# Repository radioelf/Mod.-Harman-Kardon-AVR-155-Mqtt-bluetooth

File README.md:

# Mod.-Harman-Kardon-AVR-155-Mqtt-bluetooth
Modificación amplificador Harman Kardon AVR 155, con un ESP32 para poder controlar desde MQTT y usar el modulo UDA1334a para poder reproducir música a través de bluetooth

  Creative Commons License Disclaimer
  UNLESS OTHERWISE MUTUALLY AGREED TO BY THE PARTIES IN WRITING, LICENSOR OFFERS THE WORK AS-IS
  AND MAKES NO REPRESENTATIONS OR WARRANTIES OF ANY KIND CONCERNING THE WORK, EXPRESS, IMPLIED,
  STATUTORY OR OTHERWISE, INCLUDING, WITHOUT LIMITATION, WARRANTIES OF TITLE, MERCHANTIBILITY,
  FITNESS FOR A PARTICULAR PURPOSE, NONINFRINGEMENT, OR THE ABSENCE OF LATENT OR OTHER DEFECTS,
  ACCURACY, OR THE PRESENCE OF ABSENCE OF ERRORS, WHETHER OR NOT DISCOVERABLE. SOME JURISDICTIONS
  DO NOT ALLOW THE EXCLUSION OF IMPLIED WARRANTIES, SO SUCH EXCLUSION MAY NOT APPLY TO YOU.
  EXCEPT TO THE EXTENT REQUIRED BY APPLICABLE LAW, IN NO EVENT WILL LICENSOR BE LIABLE TO YOU
  ON ANY LEGAL THEORY FOR ANY SPECIAL, INCIDENTAL, CONSEQUENTIAL, PUNITIVE OR EXEMPLARY DAMAGES
  ARISING OUT OF THIS LICENSE OR THE USE OF THE WORK, EVEN IF LICENSOR HAS BEEN ADVISED OF THE
  POSSIBILITY OF SUCH DAMAGES.
  http://creativecommons.org/licenses/by-sa/3.0/
  Author: Radioelf  http://radioelf.blogspot.com.es/

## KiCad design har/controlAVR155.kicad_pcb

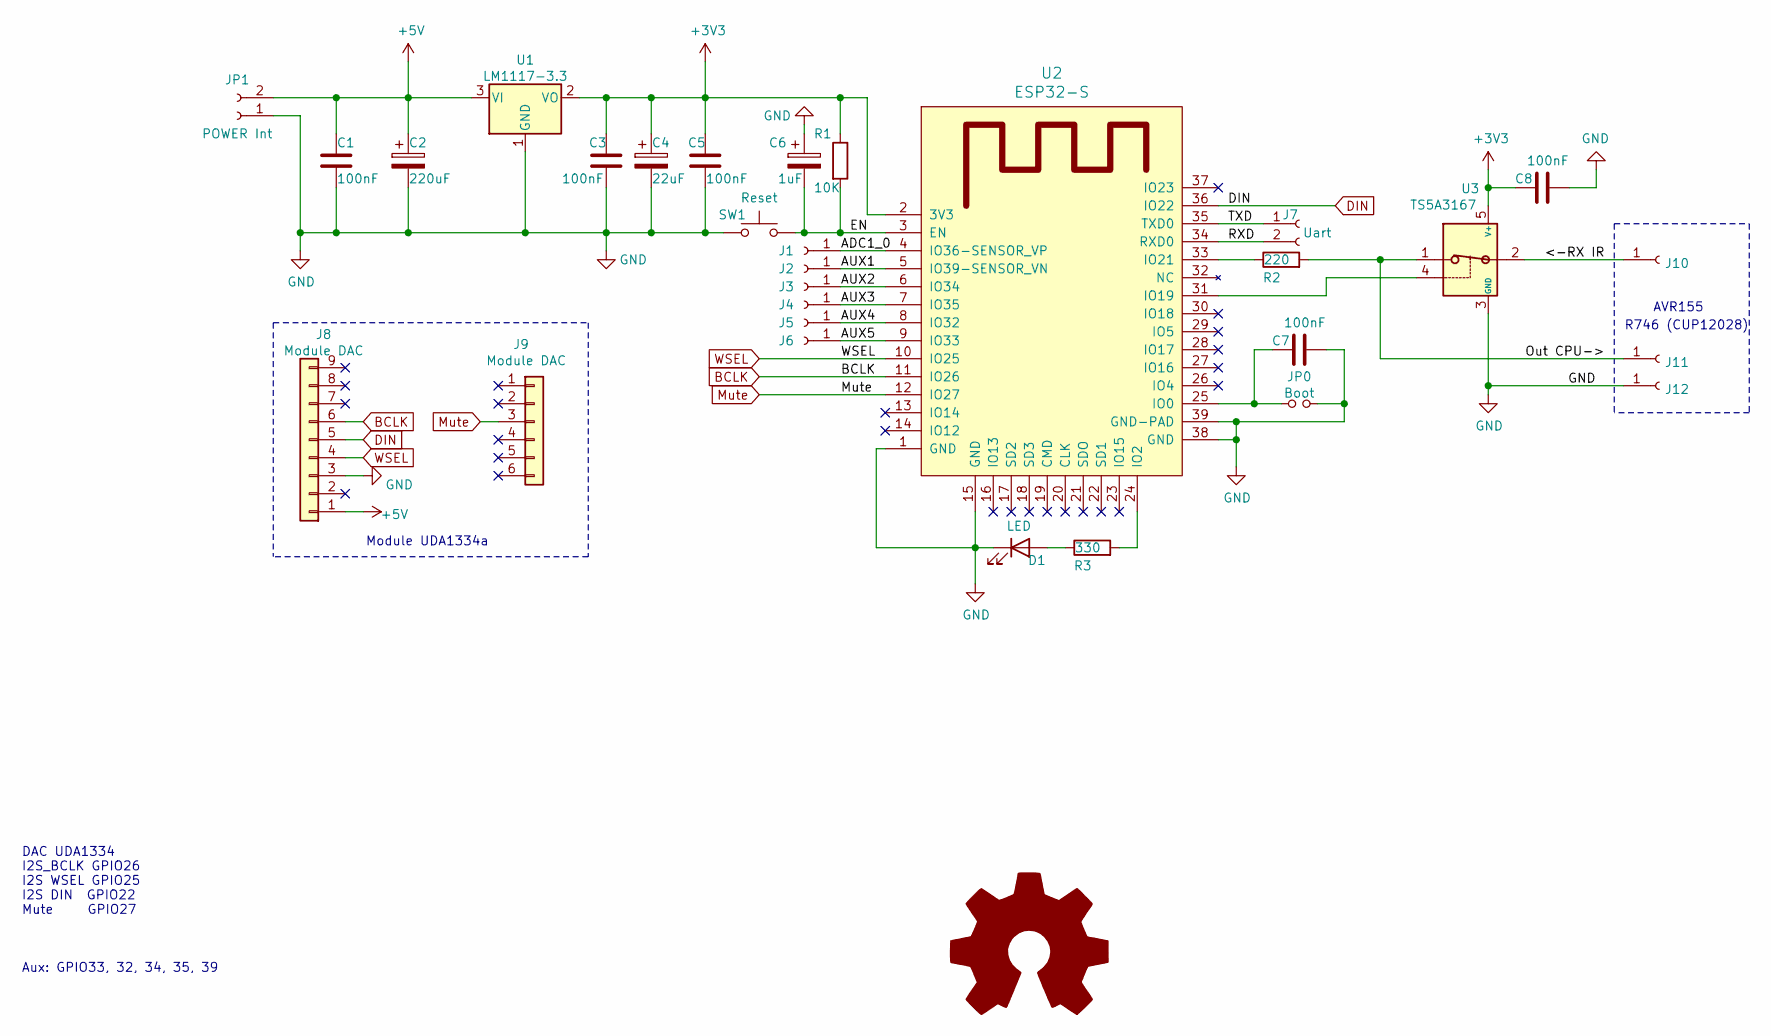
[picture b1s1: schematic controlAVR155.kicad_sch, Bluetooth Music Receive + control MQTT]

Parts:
C1, C3, C5, C7, C8: 100nF; C_0805_2012Metric
C2: 220uF; CP_Elec_6.3x3
C4: 22uF; CP_Elec_3x5.4
C6: 1uF; C_1206_3216Metric
D1: LED; LED_0402_1005Metric
J1, J2, J3, J4, J5, J6, J10, J11, J12: Conn_01x01_Female; PinHeader_1x01_P2.54mm_Vertical
J7: Uart; PinSocket_1x02_P2.54mm_Vertical
J8: Module DAC; PinHeader_1x09_P2.54mm_Vertical
J9: Module DAC; PinHeader_1x06_P2.54mm_Vertical
JP0: Boot; TestPoint_2Pads_Pitch2.54mm_Drill0.8mm
JP1: POWER Int; JST_NV_B02P-NV_1x02_P5.00mm_Vertical
R1: 10K; R_0805_2012Metric
R2: 220; R_0805_2012Metric
R3: 330; R_0805_2012Metric
SW1: Reset; SW_SPST_REED_CT05-XXXX-J1
U1: LM1117-3.3; SOT-223-3_TabPin2
U2: ESP32-S; ESP32-WROOM-32
U3: TS5A3167; SOT-23-5

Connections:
+3V3: C3.1, C4.1, C5.1, C8.1, R1.1, U1.2 (VO), U2.2 (3V3), U3.5 (V+)
+5V: C1.1, C2.1, J8.1, JP1.2, U1.3 (VI)
/<-RX IR: J10.1, U3.2
/ADC1_0: J1.1, U2.4 (IO36-SENSOR_VP)
/AUX1: J2.1, U2.5 (IO39-SENSOR_VN)
/AUX2: J3.1, U2.6 (IO34)
/AUX3: J4.1, U2.7 (IO35)
/AUX4: J5.1, U2.8 (IO32)
/AUX5: J6.1, U2.9 (IO33)
/EN: C6.2, R1.2, SW1.2, U2.3 (EN)
/Out CPU->: J11.1, R2.2, U3.1
/RXD: J7.2, U2.34 (RXD0)
/TXD: J7.1, U2.35 (TXD0)
BCLK: J8.6, U2.11 (IO26)
DIN: J8.5, U2.36 (IO22)
GND: C1.2, C2.2, C3.2, C4.2, C5.2, C6.1, C7.2, C8.2, D1.1 (K), J8.3, J12.1, JP0.2, JP1.1, SW1.1, U1.1 (GND), U2.1 (GND), U2.15 (GND), U2.38 (GND), U2.39 (GND-PAD), U3.3 (GND)
Mute: J9.3, U2.12 (IO27)
unnamed: C7.1, JP0.1, U2.25 (IO0)
unnamed: D1.2 (A), R3.1
unnamed: R2.1, U2.33 (IO21)
unnamed: R3.2, U2.24 (IO2)
unnamed: U2.31 (IO19), U3.4
WSEL: J8.4, U2.10 (IO25)

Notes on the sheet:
DAC UDA1334 I2S_BCLK GPIO26 I2S WSEL GPIO25 I2S DIN GPIO22 Mute GPIO27 Aux: GPIO33, 32, 34, 35, 39
Module UDA1334a
AVR155
R746 (CUP12028)

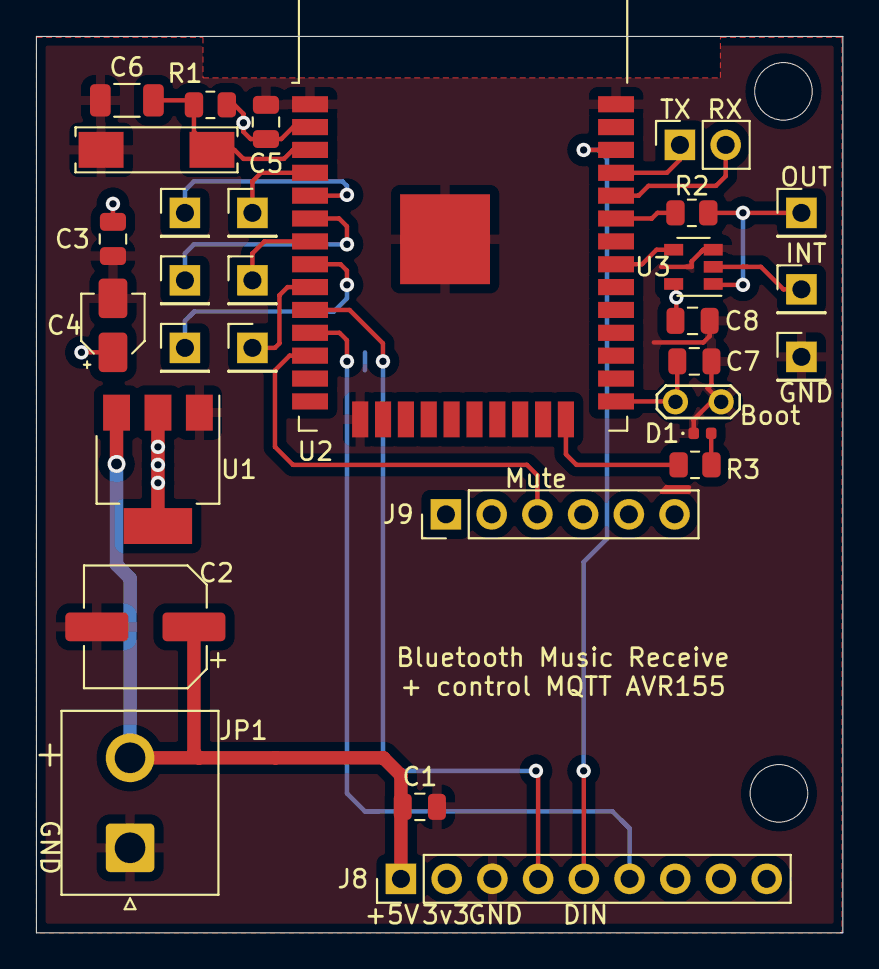
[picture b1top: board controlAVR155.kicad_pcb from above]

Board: 2 copper layers, 44.8 x 49.8 mm, 30 parts (0 on the bottom side), 23 nets.

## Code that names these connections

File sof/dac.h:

#ifndef _DAC_
#define _DAC_
/*
Modulo adafruit UDA1334a
VIN - pin y GND entrada 5V 
3VO - salida regulada de 3V3
Alimentación a 3v, señales lógicas 3v3 o 5V a excepción de PLL y SF0 de solo 3v3
WSEL - (selección de  reloj izquierdo/derecho): este es el pin que le dice al DAC 
    cuándo los datos son para el canal izquierdo o cuándo son para el canal derecho
DIN - este es el pin que recibe los datos reales, tanto los datos 
    de la izquierda como de la derecha, el pin WSEL indica cuándo se está transmitiendo a 
    la izquierda o la derecha
BCLK - este es el pin le indica al amplificador cuándo leer datos en el pin de datos.
**--OPCIONALES--**
MCLK - NO USADO
SCLK - entrada opcional de reloj del sistema de modo de video de 27 MHz; de
    forma predeterminada, generamos el reloj del sistema a partir del reloj WS en modo de 
    audio, pero el UDA también puede tomar una entrada de oscilador en este pin
Mute - este pin en alto silenciará la salida
DEEM - en el modo de audio (predeterminado), se puede usar para agregar un filtro de 
    énfasis. En el modo de video, donde el reloj del sistema se genera a partir de un 
    oscilador, esta es la salida del reloj.
PLL - establece el modo PLL, de forma predeterminada a nivel bajo para Audio. 
    Puede configurarse a pulled high o ~ 1.6V para configurar la frecuencia de video PAL o NTSC
SF0 y SF1 se utilizan para establecer el formato de datos de entrada
    SF0  SF1
     0    0   I2S
     0    1   LSB 16bits
     1    0   LSB 20bits
     1    1   LSB 24bits
AGND - masa salida audio
Rout - salida audio canal derecha (3 KΩ)
Lout - salida audio canal izquierdo (3 KΩ)

info: https://github.com/pschatzmann/ESP32-A2DP   
*/

#include "esp32_bt_music_receiver.h"                                                  // https://github.com/dvxlab/esp32_bt_music_receiver 
                                   
// I2S_BCLK      26
// I2S WSEL      25
// I2S DIN       22

BlootoothA2DSink a2d_sink;

#endif

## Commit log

2021-05-20 Create software
2021-05-20 Create info
2021-05-20 Create gerber
2021-05-20 Update software
2024-01-28 Platformio configuration file
    Fichero de configuración para platformio
2024-01-28 Update avr155.h
    Update avr155.h
